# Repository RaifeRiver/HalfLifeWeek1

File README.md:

# HalfLifeWeek1

A robot controller PCB I designed for hack club half life week 1 featuring remote control, quad 9V motor driver and battery charging.

## PCB Render
[PCB Render](https://raw.githubusercontent.com/RaifeRiver/HalfLifeWeek1/main/assets/pcb_render.png)

## Firmware
I sadly ran out of time to do firmware as I have been quite busy this week.

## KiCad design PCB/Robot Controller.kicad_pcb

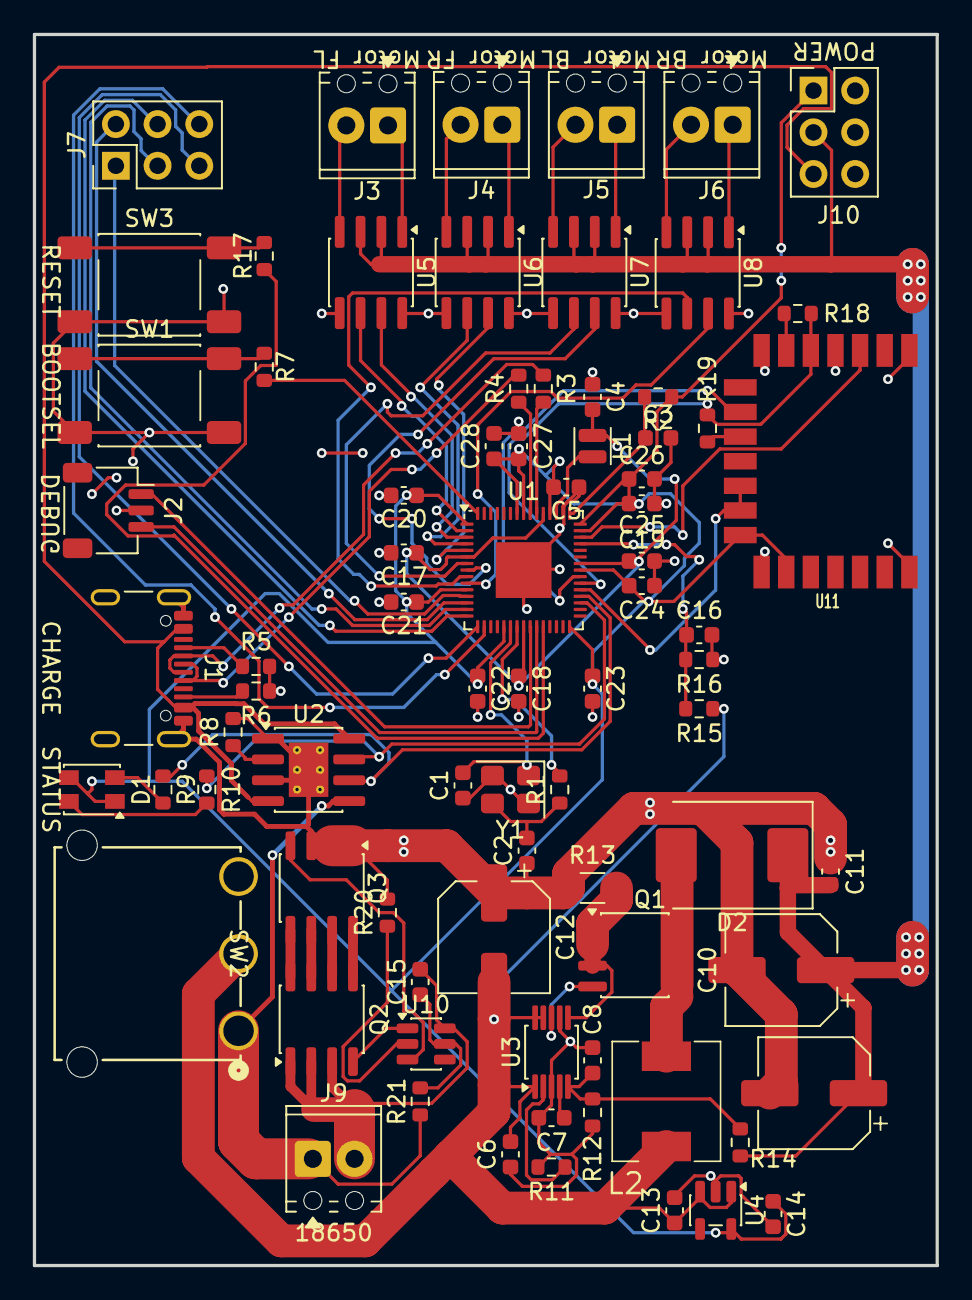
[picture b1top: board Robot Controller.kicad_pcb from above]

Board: 2 copper layers, 55.0 x 75.0 mm, 79 parts (0 on the bottom side), 70 nets.

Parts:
C1, C2: 15p; C_0603_1608Metric
C3, C4, C5: 4.7u; C_0603_1608Metric
C6, C13, C14: 1u; C_0603_1608Metric
C7: 0.22u; C_0603_1608Metric
C8: 2.2n; C_0603_1608Metric
C9, C10, C12: 68u; CP_Elec_6.3x7.7
C11, C15, C16, C17, C18, C19, C20, C21, C22, C23, C24, C25, C26, C27, C28: 0.1u; C_0603_1608Metric
D1: STATUS; LED_Kingbright_AAA3528ESGCT
D2: MBRS340T3G; D_SMC
J1: CHARGE; USB_C_Receptacle_GCT_USB4105-xx-A_16P_TopMnt_Horizontal
J2: DEBUG; JST_SH_SM03B-SRSS-TB_1x03-1MP_P1.00mm_Horizontal
J3: Motor FL; TerminalBlock_Phoenix_MPT-0,5-2-2.54_1x02_P2.54mm_Horizontal
J4: Motor FR; TerminalBlock_Phoenix_MPT-0,5-2-2.54_1x02_P2.54mm_Horizontal
J5: Motor BL; TerminalBlock_Phoenix_MPT-0,5-2-2.54_1x02_P2.54mm_Horizontal
J6: Motor BR; TerminalBlock_Phoenix_MPT-0,5-2-2.54_1x02_P2.54mm_Horizontal
J7: GPIO; PinHeader_2x03_P2.54mm_Vertical
J9: 18650; TerminalBlock_Phoenix_MPT-0,5-2-2.54_1x02_P2.54mm_Horizontal
J10: POWER; PinHeader_2x03_P2.54mm_Vertical
L1: 3.3u; L_Changjiang_FTC201610D
L2: 2.2u; ASPI-7318-2R2M-T
Q1, Q2, Q3: FDS6680A; SO-8_3.9x4.9mm_P1.27mm
R1, R7, R17: 1k; R_0603_1608Metric
R2: 33; R_0603_1608Metric
R3, R4: 27; R_0603_1608Metric
R5, R6: 5.1k; R_0603_1608Metric
R8: 1.2k; R_0603_1608Metric
R9, R10: 330; R_0603_1608Metric
R11, R15, R16: 100k; R_0603_1608Metric
R12: 24.9k; R_0603_1608Metric
R13: 0.02; R_1206_3216Metric
R14: 154k; R_0603_1608Metric
R18, R21: 470; R_0603_1608Metric
R19: 10k; R_0603_1608Metric
R20: 2k; R_0603_1608Metric
SW1: BOOTSEL; SW_Push_1P1T_NO_E-Switch_TL3301NxxxxxG
SW2: POWER; SPDT-1101M2_CNK
SW3: RESET; SW_Push_1P1T_NO_E-Switch_TL3301NxxxxxG
U1: RP2354A; QFN-60-1EP_7x7mm_P0.4mm_EP3.4x3.4mm
U2: TP4056; SOIC-8-1EP_3.9x4.9mm_P1.27mm_EP2.41x3.3mm_ThermalVias
U3: MAX668; MSOP-10_3x3mm_P0.5mm
U4: AP2112K-3.3; SOT-23-5
U5, U6, U7, U8: L9110; SOIC-8_3.9x4.9mm_P1.27mm
U10: DW01A; SOT-23-6
U11: RPi RM2; rpi_rmc20452t
Y1: 12MHz; Crystal_SMD_Abracon_ABM8G-4Pin_3.2x2.5mm

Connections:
+1V1: C4.2, C17.1, C18.1, C19.1, L1.1, U1.6 (DVDD), U1.23 (DVDD), U1.39 (DVDD), U1.50 (VREG_FB)
+3V3: C5.2, C14.1, C20.1, C21.1, C22.1, C23.1, C24.1, C25.1, C26.1, C27.1, C28.1, D1.1 (A1), D1.3 (A2), J10.1, R2.1, U1.1 (IOVDD), U1.11 (IOVDD), U1.20 (IOVDD), U1.30 (IOVDD), U1.38 (IOVDD), U1.44 (ADC_AVDD), U1.45 (IOVDD), U1.49 (VREG_VIN), U1.53 (USB_OTP_VDD), U1.54 (QSPI_IOVDD), U4.5 (VOUT), U11.14 (VDDIO), U11.16 (VIN)
+5V: J1.A4 (VBUS), J1.A9 (VBUS), J1.B4 (VBUS), J1.B9 (VBUS), J10.5, U2.4 (V_{CC}), U2.8 (CE)
+9V: C9.1, C10.1, C11.1, D2.1 (K), J10.3, R14.1, U5.2, U5.3, U6.2, U6.3, U7.2, U7.3, U8.2, U8.3
+BATT: C6.2, C12.2, C13.1, L2.1, R15.2, SW2.2 (B), U3.1, U3.9, U3.10, U4.1 (VIN), U4.3 (EN)
GND: C1.1, C2.1, C3.2, C4.1, C5.1, C6.1, C7.1, C8.1, C9.2, C10.2, C11.2, C12.1, C13.2, C14.2, C16.1, C17.2, C18.2, C19.2, C20.2, C21.2, C22.2, C23.2, C24.2, C25.2, C26.2, C27.2, C28.2, J1.A1 (GND), J1.A12 (GND), J1.B1 (GND), J1.B12 (GND), J1.SH (SHIELD), J2.2, J10.2, J10.4, J10.6, Q3.1 (D), Q3.2 (G), Q3.3 (S), R5.2, R6.1, R8.2, R11.1, R12.1, R13.2, R16.2, R20.2, SW1.2, SW3.2, U1.47 (VREG_PGND), U1.61 (GND), U2.1 (TEMP), U2.3 (GND), U2.9 (EPAD), U3.3, U3.7, U4.2 (GND), U5.5, U5.8, U6.5, U6.8, U7.5, U7.8, U8.5, U8.8, U11.1 (GND), U11.4 (GND), U11.7 (GND), U11.15 (GND), U11.21 (GND), Y1.2 (G), Y1.4 (G)
unnamed: C2.2, R1.1, Y1.3
unnamed: D1.2 (K1), R10.1
unnamed: D1.4 (K2), R9.2
unnamed: D2.2 (A), L2.2, Q1.5, Q1.6, Q1.7, Q1.8
unnamed: J1.A5 (CC1), R5.1
unnamed: J1.B5 (CC2), R6.2
unnamed: J1.A6 (D+), J1.B6 (D+), R4.2
unnamed: J1.A7 (D-), J1.B7 (D-), R3.1
unnamed: J2.1, U1.24 (SWCLK)
unnamed: J2.3, U1.25 (SWDIO)
unnamed: J3.1, U5.1
unnamed: J3.2, U5.4
unnamed: J4.1, U6.1
unnamed: J4.2, U6.4
unnamed: J5.1, U7.1
unnamed: J5.2, U7.4
unnamed: J6.1, U8.1
unnamed: J6.2, U8.4
unnamed: J9.1 (+), R21.1, SW2.1 (A), U2.5 (BAT)
unnamed: C15.2, J9.2 (-), Q2.1 (D), Q2.2 (G), Q2.3 (S), U10.6 (GND)
unnamed: Q1.4, U3.8
unnamed: Q1.1 (D), Q1.2 (G), Q1.3 (S), R13.1, U3.6
unnamed: Q2.5, Q2.6, Q2.7, Q2.8, Q3.5, Q3.6, Q3.7, Q3.8
unnamed: Q2.4, U10.1 (OD)
unnamed: Q3.4, U10.3 (OC)
unnamed: R7.1, SW1.1
unnamed: R17.2, SW3.1
unnamed: U1.2 (GPIO0), U5.6
unnamed: U1.3 (GPIO1), U5.7
unnamed: U1.4 (GPIO2), U6.6
unnamed: U1.5 (GPIO3), U6.7
unnamed: U1.7 (GPIO4), U7.6
unnamed: U1.8 (GPIO5), U7.7
unnamed: U1.9 (GPIO6), U8.6
unnamed: U1.10 (GPIO7), U8.7
unnamed: J7.1, U1.12 (GPIO8)
unnamed: J7.2, U1.13 (GPIO9)
unnamed: J7.3, U1.14 (GPIO10)
unnamed: J7.4, U1.15 (GPIO11)
unnamed: J7.5, U1.16 (GPIO12)
unnamed: J7.6, U1.17 (GPIO13)
unnamed: R10.2, U1.33 (GPIO21), U2.7 (~CHRG)
unnamed: R9.1, U1.34 (GPIO22), U2.6 (~STDBY)
unnamed: U1.35 (GPIO23), U11.12 (WL_ON), U11.13 (BT_ON)
unnamed: R18.2, R19.2, U1.36 (GPIO24), U11.5 (DI)
unnamed: U1.37 (GPIO25), U11.9 (CS)
unnamed: C16.2, R15.1, R16.1, U1.42 (GPIO28/ADC2)
unnamed: U1.43 (GPIO29/ADC3), U11.3 (SCLK)
unnamed: R17.1, U1.26 (RUN)
unnamed: R3.2, U1.51 (USB_DM)
unnamed: R4.1, U1.52 (USB_DP)
unnamed: C3.1, R2.2, U1.46 (VREG_AVDD)
unnamed: L1.2, U1.48 (VREG_LX)
unnamed: C1.2, U1.21 (XIN), Y1.1
unnamed: R1.2, U1.22 (XOUT)
unnamed: R7.2, U1.60 (~QSPI_SS)
unnamed: R8.1, U2.2 (PROG)
unnamed: R11.2, U3.2
unnamed: C7.2, U3.4
unnamed: C8.2, R12.2, R14.2, U3.5
unnamed: R20.1, U10.2 (CS)
unnamed: C15.1, R21.2, U10.5 (VCC)
unnamed: R18.1, U11.6 (DO)
unnamed: R19.1, U11.10 (nIRQ)
